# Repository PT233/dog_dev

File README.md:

# desktop_tracking_robot

基于 ROS 2 Jazzy、GStreamer、YOLOv8、ByteTrack、Raspberry Pi 和 STM32F103 的桌面目标跟随机器人。

本文档集已按当前重构后的代码树重新整理，基线日期为 `2026-04-28`。默认运行链路是：

`gst_receiver -> stereo_splitter -> detection_node -> tracker_node -> behavior_node -> leg_motion_node -> uart_bridge -> STM32`

## 从哪里开始

- [QUICK_START.md](QUICK_START.md): 已完成环境准备后的最短启动路径
- [SETUP_GUIDE.md](SETUP_GUIDE.md): 按主机划分的构建、部署、接线和环境准备
- [ARCHITECTURE.md](ARCHITECTURE.md): 当前代码结构、运行时拓扑、消息接口和协议摘要
- [docs/README.md](docs/README.md): 专题文档索引
- [hardware_wiring.html](hardware_wiring.html): 接线图

## 当前代码主链

### WSL2 / PC

- `gst_receiver_node`: 接收树莓派发来的 `UDP/H.264` 视频并发布 `/stereo/image_raw`
- `stereo_splitter_node`: 从 `640x480` 双目拼接图中裁出左目，发布 `~/input/image`
- `detection_node`: 运行 YOLOv8 ONNX 推理，发布 `/detection_node/output/detections`
- `tracker_node`: 给检测结果分配稳定轨迹 ID，发布 `/tracker_node/output/tracked_objects`
- `behavior_node`: 按目标类别筛选目标并发布 `/behavior_node/output/pixel_error`
- `leg_motion_node`: 把像素误差转换为四足舵机角命令，发布 `/leg_motion_node/output/servo_command`

### Raspberry Pi

- `scripts/start_camera_stream.sh`: `/dev/video0 -> H.264 -> UDP:5600`
- `uart_bridge_node`: `/leg_motion_node/output/servo_command -> UART`，`UART -> /uart_bridge_node/output/servo_state`

### STM32

- `Task_UART_RX`: DMA + IDLE 收帧、握手、分发舵机命令
- `Task_Traj_Planner`: 5 ms 周期梯形轨迹插值
- `Task_Status_TX`: 50 ms 周期上报 `SERVO_STATE_V2` 和 `SYSTEM_STATE`
- `Task_Safety`: IWDG 喂狗

## 仓库结构

```text
dog_dev/
├── README.md
├── QUICK_START.md
├── SETUP_GUIDE.md
├── ARCHITECTURE.md
├── hardware_wiring.html
├── config/                    # 顶层共享参数文件
├── docs/                      # 专题文档
├── models/                    # YOLO 模型与 COCO 标签
├── ros2_ws/
│   └── src/
│       ├── robot_bringup
│       ├── robot_interfaces
│       ├── gst_receiver
│       ├── stereo_splitter
│       ├── detection_node
│       ├── tracker_node
│       ├── behavior_node
│       ├── visual_servo
│       └── uart_bridge
├── scripts/                   # 启动、部署和网络配置脚本
├── shared/                    # ROS 侧与 STM32 侧共享头文件/小工具
├── stm32_keil/                # STM32F103 工程
└── tests/                     # 离线测试与验证脚本
```

## 最常用命令

### WSL2 构建

```bash
source /opt/ros/jazzy/setup.bash
export ONNXRUNTIME_ROOT=/path/to/onnxruntime
cd /home/peter/dog/dog_dev/ros2_ws
colcon build
source install/setup.bash
```

### WSL2 启动视觉栈

```bash
source /opt/ros/jazzy/setup.bash
cd /home/peter/dog/dog_dev
source ros2_ws/install/setup.bash
export ROBOT_DDS_ROLE=wsl
source scripts/ros2_network_env.sh
ros2 launch robot_bringup vision_stack.launch.py
```

### 树莓派启动

```bash
cd /home/ubuntu/desktop_tracking_robot
./scripts/rpi_start_camera.sh <WSL_IP> 5600
./scripts/rpi_start_ros.sh
```

### 无硬件联调

```bash
source /opt/ros/jazzy/setup.bash
cd /home/peter/dog/dog_dev
source ros2_ws/install/setup.bash
ros2 launch robot_bringup test_73_complete.launch.py
```

## 当前约束

- `detection_node` 构建依赖 `ONNXRUNTIME_ROOT`
- `vision_front` 是可选的进程内组合可执行文件，默认 `BUILD_VISION_FRONT=OFF`
- `detection_viz_node` 仅用于调试，不在默认 launch 链路中
- `robot_interfaces/srv/CalibrateCenter.srv` 目前只有接口定义，代码里还没有服务端实现

## 文档维护规则

- 只要 launch、可执行文件名、topic/service、共享协议或部署脚本有变化，就同步更新顶层文档和 `docs/`
- `progress.md` 保存当前状态快照，不再维护旧式逐任务流水账
- `task.md` 保存当前待办，不再对应旧的阶段式生成任务模板

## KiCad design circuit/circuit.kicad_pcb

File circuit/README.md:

# Blue Pill SG90 Breadboard Carrier

本工程已从 `circuit/pcb.md` 重绘为 KiCad 9.0.9 可加载版本。

## 当前规则

- 板框：71.0 mm x 56.0 mm，来自 `circuit/pcb.md` 的 `Edge.Cuts`。
- 层数：2 层，F.Cu / B.Cu。
- Blue Pill：H1/H2 两条 1x20 排母，PCB 内显式分配网络。
- 面包板引出：B1A/B1B/B2A/B2B 四排 20 孔，共 80 个引出孔。
- SG90：J1/J2/J3/J4，物理顺序 G-V-S。
- UART：J7，丝印顺序 G PA10 PA9。
- 覆铜：B.Cu GND zone 已按当前板框重新生成，避免保留 KiCad 10 的不兼容填充块。

## 预览命令

```bash
SHARUN_DIR=/opt/kicad9 /opt/kicad9/sharun kicad /home/peter/dog/dog_dev/circuit/circuit.kicad_pro
SHARUN_DIR=/opt/kicad9 /opt/kicad9/sharun pcbnew /home/peter/dog/dog_dev/circuit/circuit.kicad_pcb
```

## 生成文件

- PCB：`circuit.kicad_pcb`
- 原理图说明：`circuit.kicad_sch`
- 校验报告：`reports/layout_validation.json`
- BOM：`reports/bom.csv`

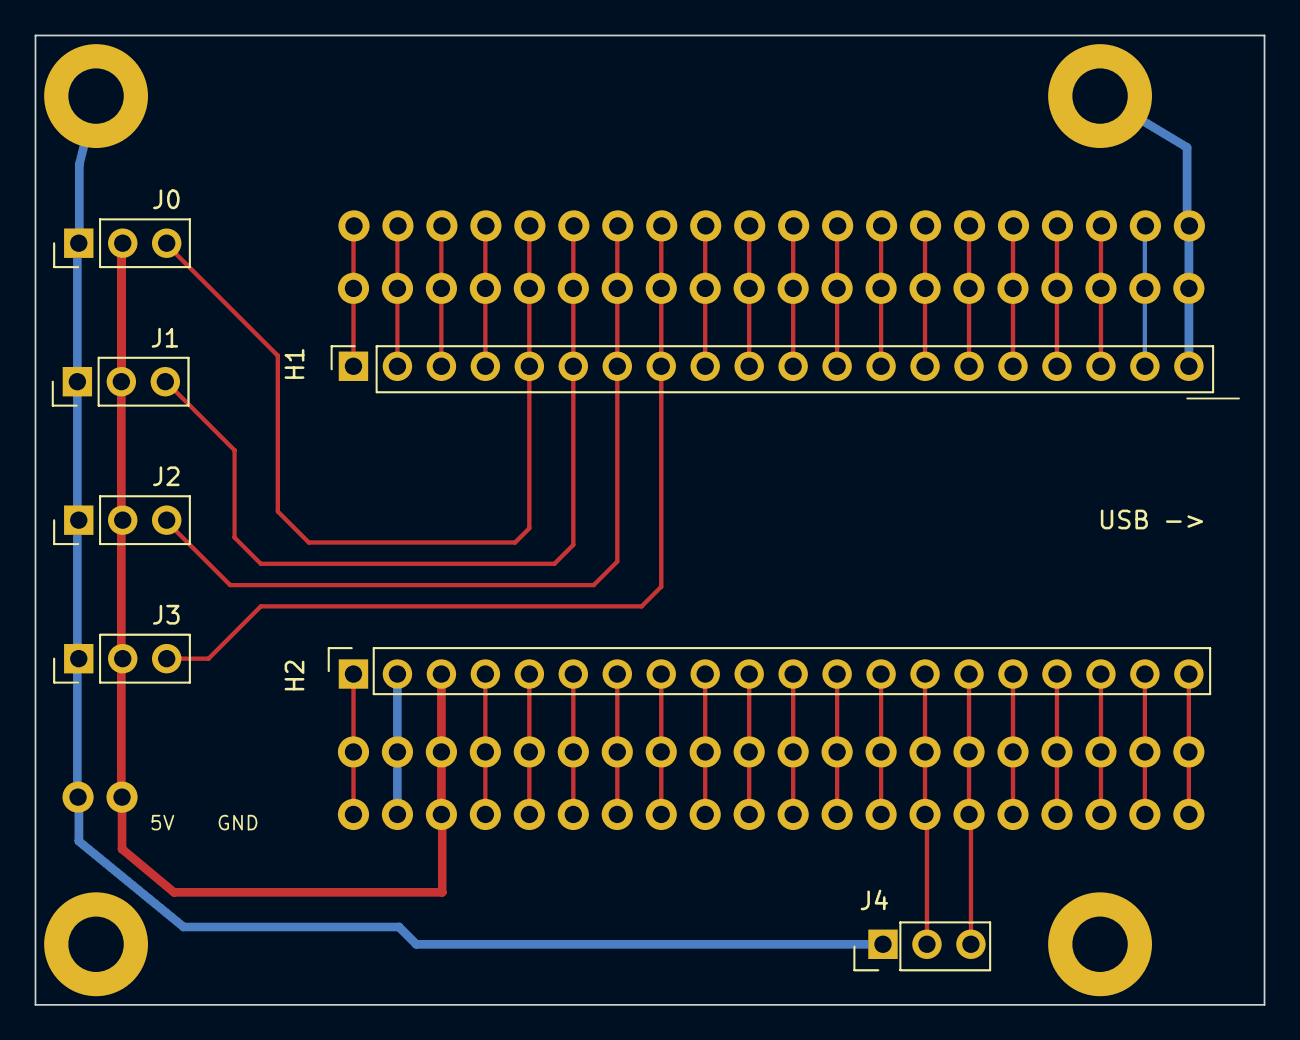
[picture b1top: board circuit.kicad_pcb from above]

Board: 2 copper layers, 71.0 x 56.0 mm, 16 parts (0 on the bottom side), 38 nets.

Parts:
B1A: Top_20_Pin_Breadboard_Row_Near
B1B: Top_20_Pin_Breadboard_Row_Far
B2A: Bottom_20_Pin_Breadboard_Row_Near
B2B: Bottom_20_Pin_Breadboard_Row_Far
H1: BluePill_Row_A_1x20
H2: BluePill_Row_B_1x20
J2, J2#2, J2#3, J2#4: SG90_FR_GVS
J5: 5V_SERVO_IN_GND
J7: UART_G_PA9_PA10
MH1, MH2, MH3, MH4: Raspberry_Pi_4B_Aligned_Mount_3.2mm_6mmPad

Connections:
3V3: B2A.1, B2B.1, H2.1
3V3_H1: B1A.18, B1B.18, H1.18
5V_SERVO: B2A.3, B2B.3, H2.3, J2.2, J2#2.2, J2#3.2, J2#4.2, J5.1
GND: B1A.19, B1A.20, B1B.19, B1B.20, B2A.2, B2B.2, H1.19, H1.20, H2.2, J2.1, J2#2.1, J2#3.1, J2#4.1, J5.2, J7.1, MH1.1, MH2.1, MH3.1, MH4.1
PA0_PWM_FL: B1A.5, B1B.5, H1.5, J2.3
PA1_PWM_FR: B1A.6, B1B.6, H1.6, J2#4.3
PA2_PWM_RL: B1A.7, B1B.7, H1.7, J2#3.3
PA3_PWM_RR: B1A.8, B1B.8, H1.8, J2#2.3
PA4: B1A.9, B1B.9, H1.9
PA5: B1A.10, B1B.10, H1.10
PA6: B1A.11, B1B.11, H1.11
PA7: B1A.12, B1B.12, H1.12
PA8: B2A.16, B2B.16, H2.16
PA9_TX: B2A.15, B2B.15, H2.15, J7.3
PA10_RX: B2A.14, B2B.14, H2.14, J7.2
PA11: B2A.13, B2B.13, H2.13
PA12: B2A.12, B2B.12, H2.12
PA15: B2A.11, B2B.11, H2.11
PB0: B1A.13, B1B.13, H1.13
PB1: B1A.14, B1B.14, H1.14
PB3: B2A.10, B2B.10, H2.10
PB4: B2A.9, B2B.9, H2.9
PB5: B2A.8, B2B.8, H2.8
PB6: B2A.7, B2B.7, H2.7
PB7: B2A.6, B2B.6, H2.6
PB8: B2A.5, B2B.5, H2.5
PB9: B2A.4, B2B.4, H2.4
PB10: B1A.15, B1B.15, H1.15
PB11: B1A.16, B1B.16, H1.16
PB12: B2A.20, B2B.20, H2.20
PB13: B2A.19, B2B.19, H2.19
PB14: B2A.18, B2B.18, H2.18
PB15: B2A.17, B2B.17, H2.17
PC13: B1A.2, B1B.2, H1.2
PC14: B1A.3, B1B.3, H1.3
PC15: B1A.4, B1B.4, H1.4
RST: B1A.17, B1B.17, H1.17
VBAT: B1A.1, B1B.1, H1.1

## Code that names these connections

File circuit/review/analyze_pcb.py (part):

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        width_issues.append({"net": net, "class": klass, "width": s["width"], "expected": expected, "start": s["start"], "end": s["end"]})

pwm_lengths = {}
for net in ["PA0_PWM_FL", "PA1_PWM_FR", "PA2_PWM_RL", "PA3_PWM_RR"]:
    total = sum(distance(s["start"], s["end"]) for s in segments if s["net"] == net)
    pwm_lengths[net] = total

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
pwm_pad_routes = {}
pwm_specs = [
    ("PA0_PWM_FL", "H1", "5", "J1", "3"),
    ("PA1_PWM_FR", "H1", "6", "J2", "3"),
    ("PA2_PWM_RL", "H1", "7", "J3", "3"),
    ("PA3_PWM_RR", "H1", "8", "J4", "3"),
]
for net, href, hpad, jref, jpad in pwm_specs:
    hfp = refs.get(href)
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
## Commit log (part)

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2026-04-23 create
2026-04-23 任务0.1
2026-04-23 任务0.2
2026-04-23 任务1.4
2026-04-23 任务1.5
2026-04-23 任务2.1
2026-04-23 任务2.2
2026-04-23 任务2.3
2026-04-23 任务2.4
2026-04-23 任务2.5
2026-04-23 任务2.6& 2.7
2026-04-23 任务3.1
2026-04-23 任务3.6& 3.7
2026-04-24 stop tracking log and build directories
2026-04-24 任务4.1 - 4.4
2026-04-24 任务4.5 & 4.6
2026-04-24 硬件准备
2026-04-26 rm log/ ros2_ws/log/ ros2_ws/src/log/ build/ stm32_fw/build/
2026-04-26 chdir
2026-04-26 P3 进度文档：标记核心代码完成，三个包编译成功
2026-04-26 push
2026-04-27 openocd 2 keil
2026-04-27 调整uart协议，修改dds传输协议
2026-04-28 重构+文档
2026-04-29 更新说明文档
2026-04-29 修正中文注释
2026-04-29 修改代码标准化为micro-ros，已通过编译，差测试
2026-05-05 增加电路板开发，嘉立创已下单。
2026-05-05 删除历史信息
